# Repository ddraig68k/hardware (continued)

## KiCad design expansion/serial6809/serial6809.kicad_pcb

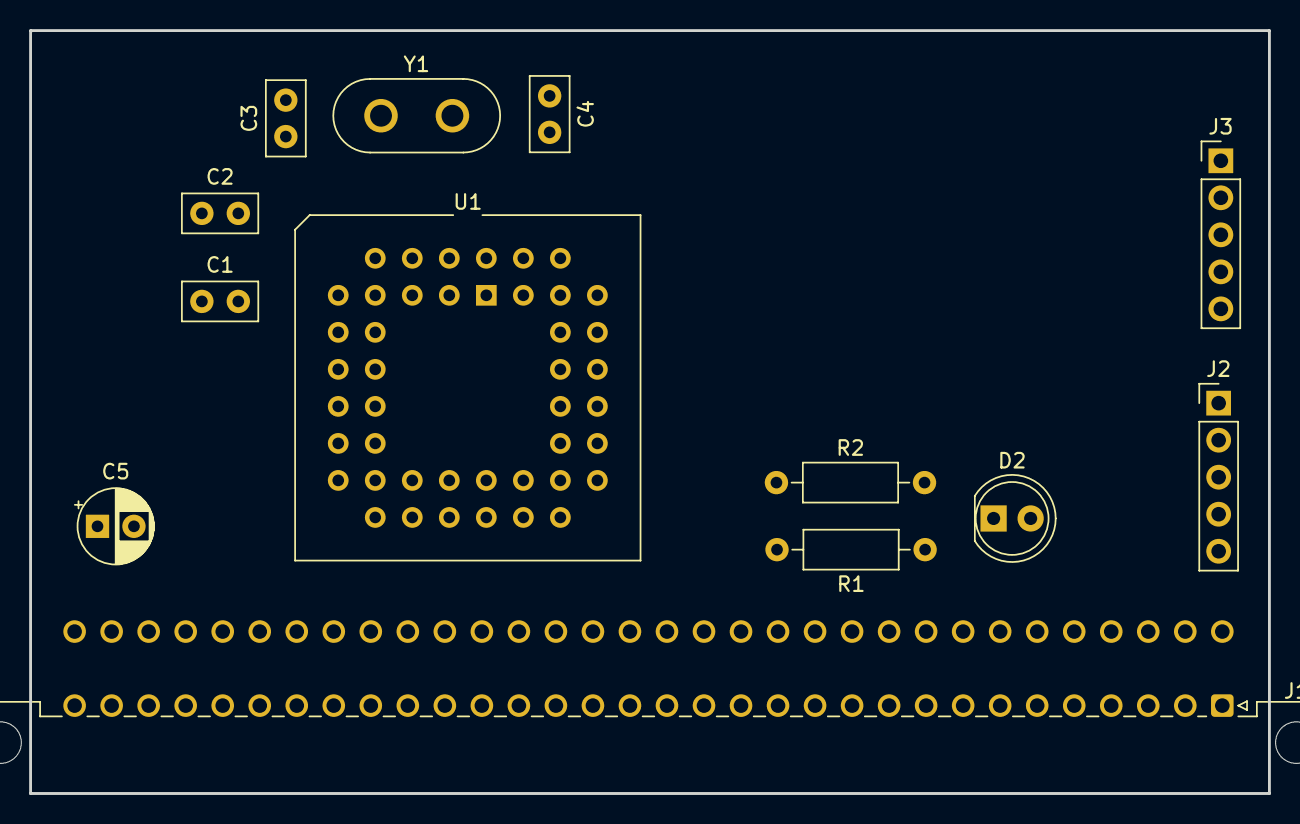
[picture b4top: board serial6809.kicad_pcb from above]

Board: 2 copper layers, 85.0 x 52.3 mm, 13 parts (0 on the bottom side), 30 nets, no tracks yet.

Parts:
C1, C2: 100nF; C_Disc_D5.0mm_W2.5mm_P2.50mm
C3, C4: 22pF; C_Disc_D5.0mm_W2.5mm_P2.50mm
C5: 47uF; CP_Radial_D5.0mm_P2.50mm
D2: GREEN; LED_D5.0mm
J1: Expansion; DIN41612_C_2x32_Male_Horizontal_THT
J2: Serial 2; PinHeader_1x05_P2.54mm_Vertical
J3: Serial 1; PinHeader_1x05_P2.54mm_Vertical
R1: 10K; R_Axial_DIN0207_L6.3mm_D2.5mm_P10.16mm_Horizontal
R2: 270R; R_Axial_DIN0207_L6.3mm_D2.5mm_P10.16mm_Horizontal
U1: SC26C92C1A; PLCC-44_THT-Socket
Y1: 3.6864Mhz; Crystal_HC50_Vertical

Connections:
+5V: C1.1, C2.1, C5.1, J1.A1, J1.C1, R1.1, U1.44 (VCC)
/A0: J1.C30, U1.2 (A0)
/A1: J1.C29, U1.4 (A1)
/A2: J1.C28, U1.6 (A2)
/A3: J1.C27, U1.7 (A3)
/CTSA: J3.4, U1.8 (IP0)
/CTSB: J2.4, U1.5 (IP1)
/D0: J1.A12, U1.28 (D0)
/D1: J1.A11, U1.18 (D1)
/D2: J1.A10, U1.27 (D2)
/D3: J1.A9, U1.19 (D3)
/D4: J1.A8, U1.26 (D4)
/D5: J1.A7, U1.20 (D5)
/D6: J1.A6, U1.25 (D6)
/D7: J1.A5, U1.21 (D7)
/RESET: J1.C6, U1.38 (RESET)
/RTSA: J3.3, U1.32 (OP0)
/RTSB: J2.3, U1.14 (OP1)
/RXDA: J3.1, U1.33 (TxDA)
/RXDB: J2.1, U1.13 (TxDB)
/TXDA: J3.2, U1.35 (RxDA)
/TXDB: J2.2, U1.11 (RxDB)
/~CS_EXP: D2.2 (A), J1.A15, U1.39 (~CE)
/~INT_EXP1: J1.A13, R1.2, U1.24 (~INTR)
/~RD: J1.A22, U1.10 (~RD)
/~WR: J1.A21, U1.9 (~WR)
GND: C1.2, C2.2, C3.2, C4.2, C5.2, J1.A31, J1.A32, J1.C31, J1.C32, J2.5, J3.5, R2.2, U1.22 (GND)
unnamed: D2.1 (K), R2.1
unnamed: C4.1, U1.36 (X1/CLK), Y1.2
unnamed: C3.1, U1.37 (X2), Y1.1

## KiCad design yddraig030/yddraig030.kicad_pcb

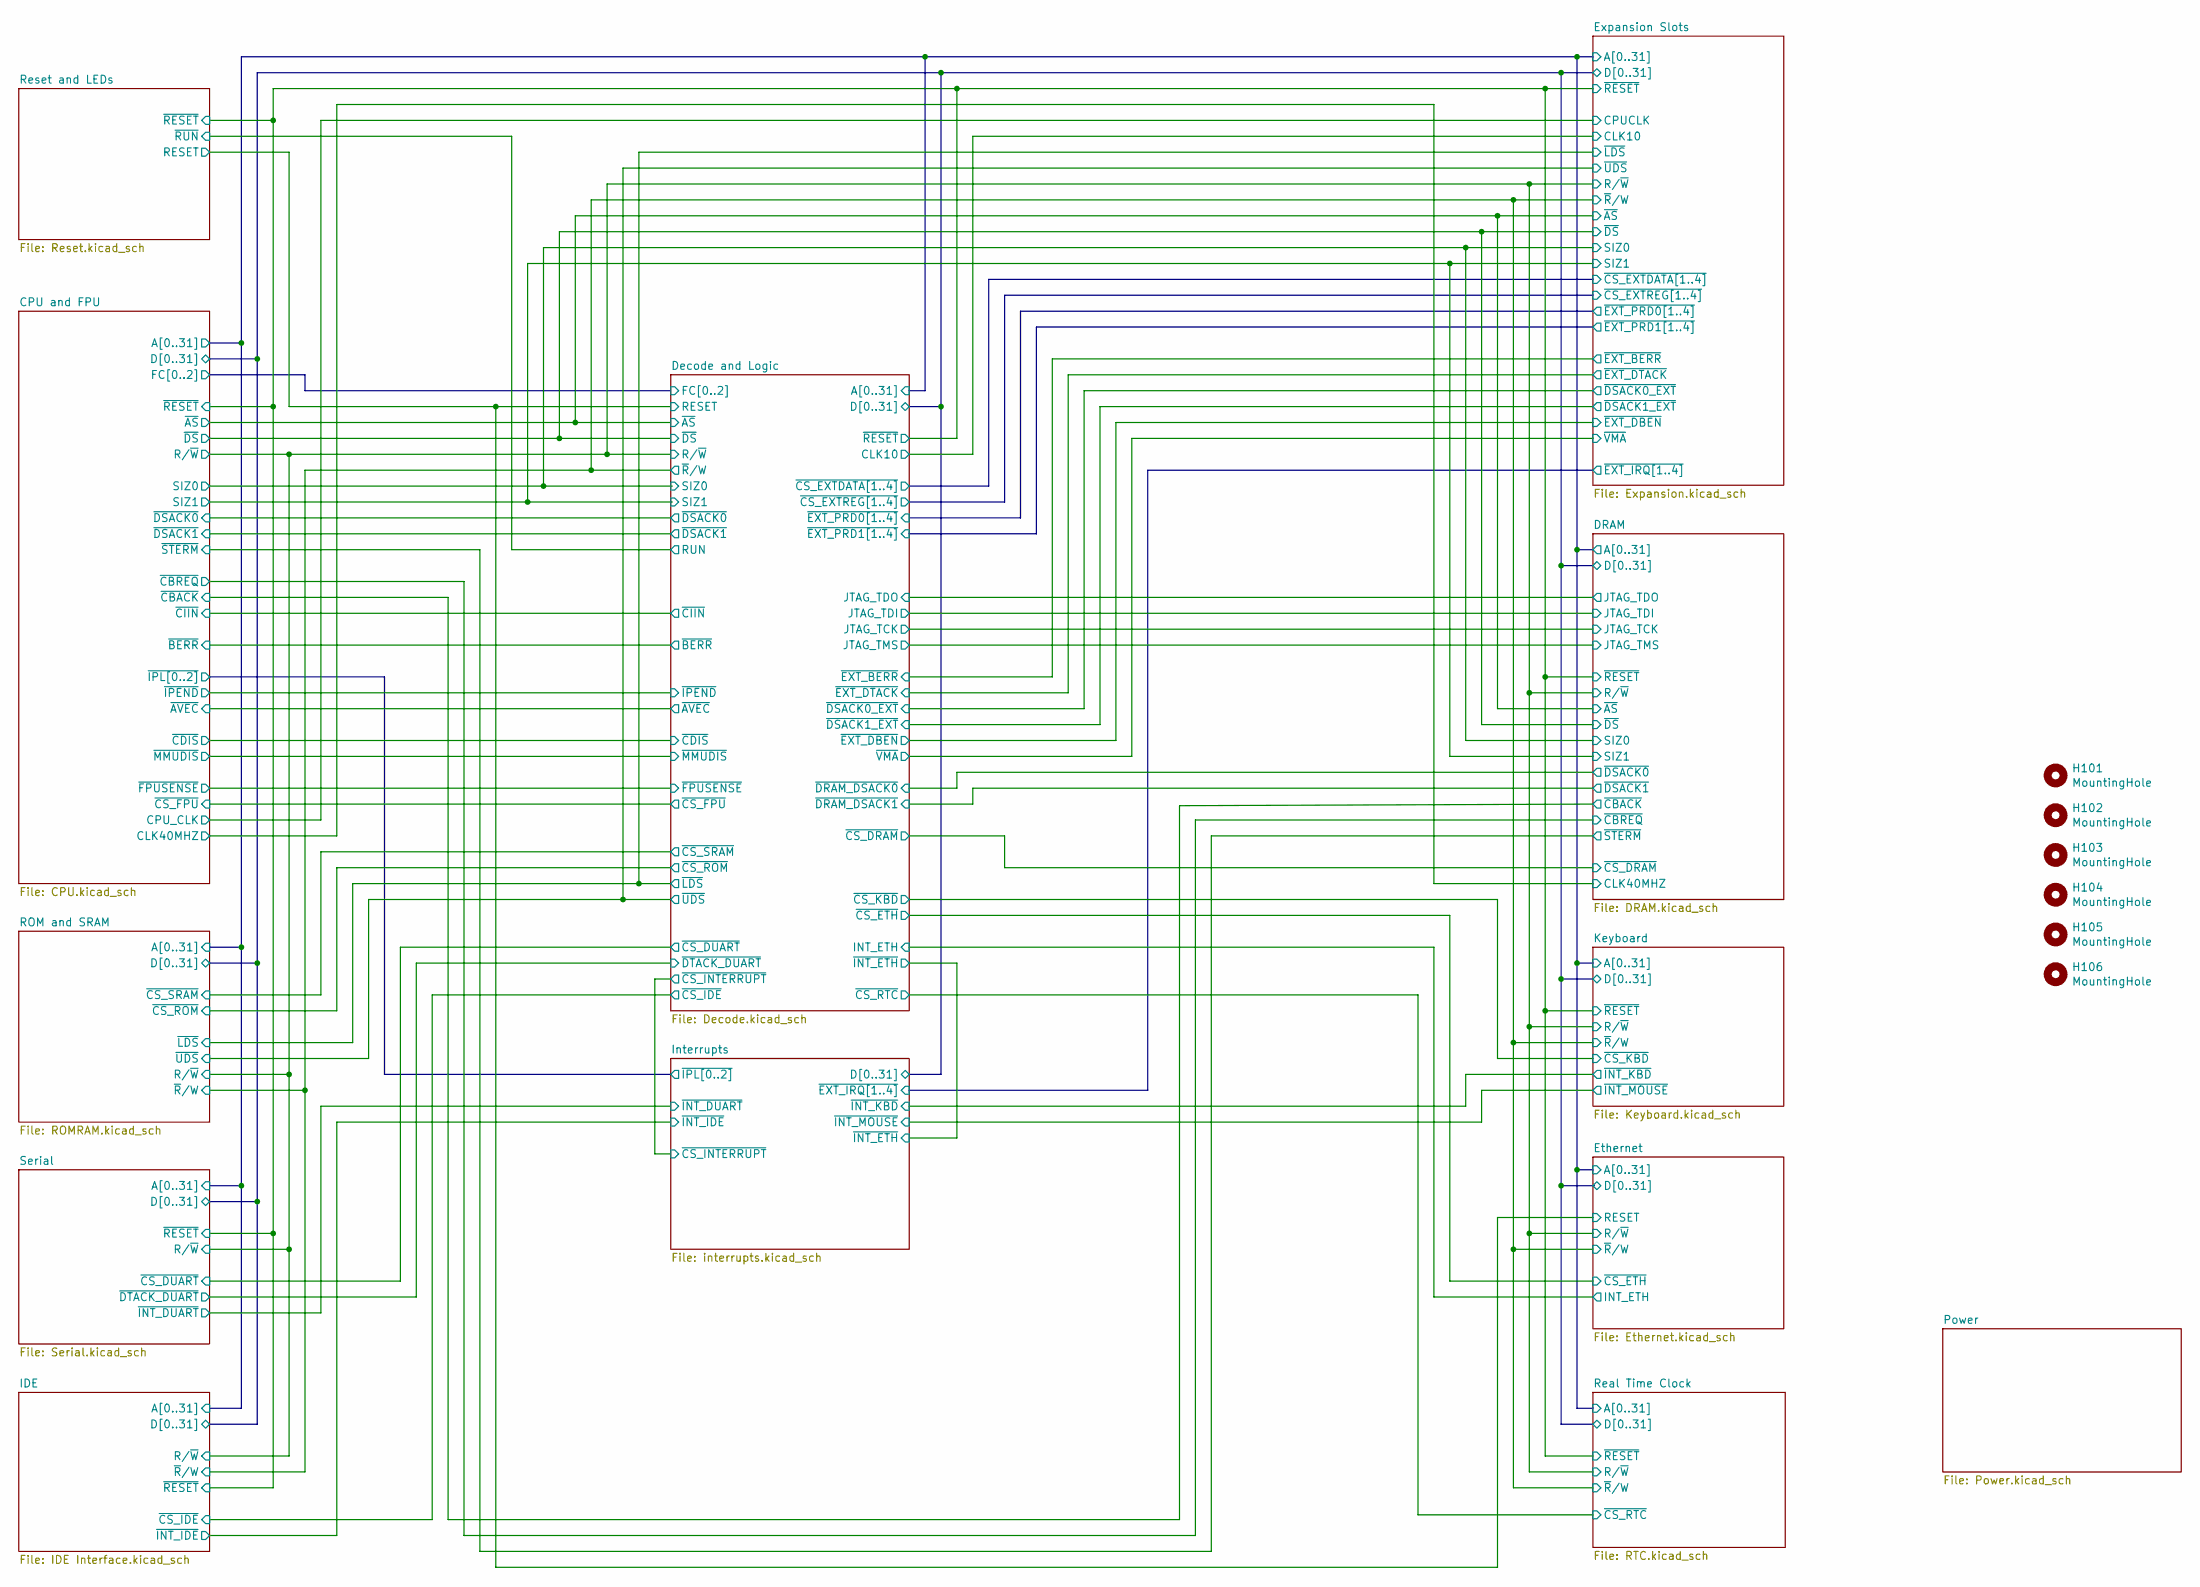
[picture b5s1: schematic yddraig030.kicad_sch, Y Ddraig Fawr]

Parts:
H101, H102, H103, H104, H105, H106: MountingHole; MountingHole_4.3mm_M4

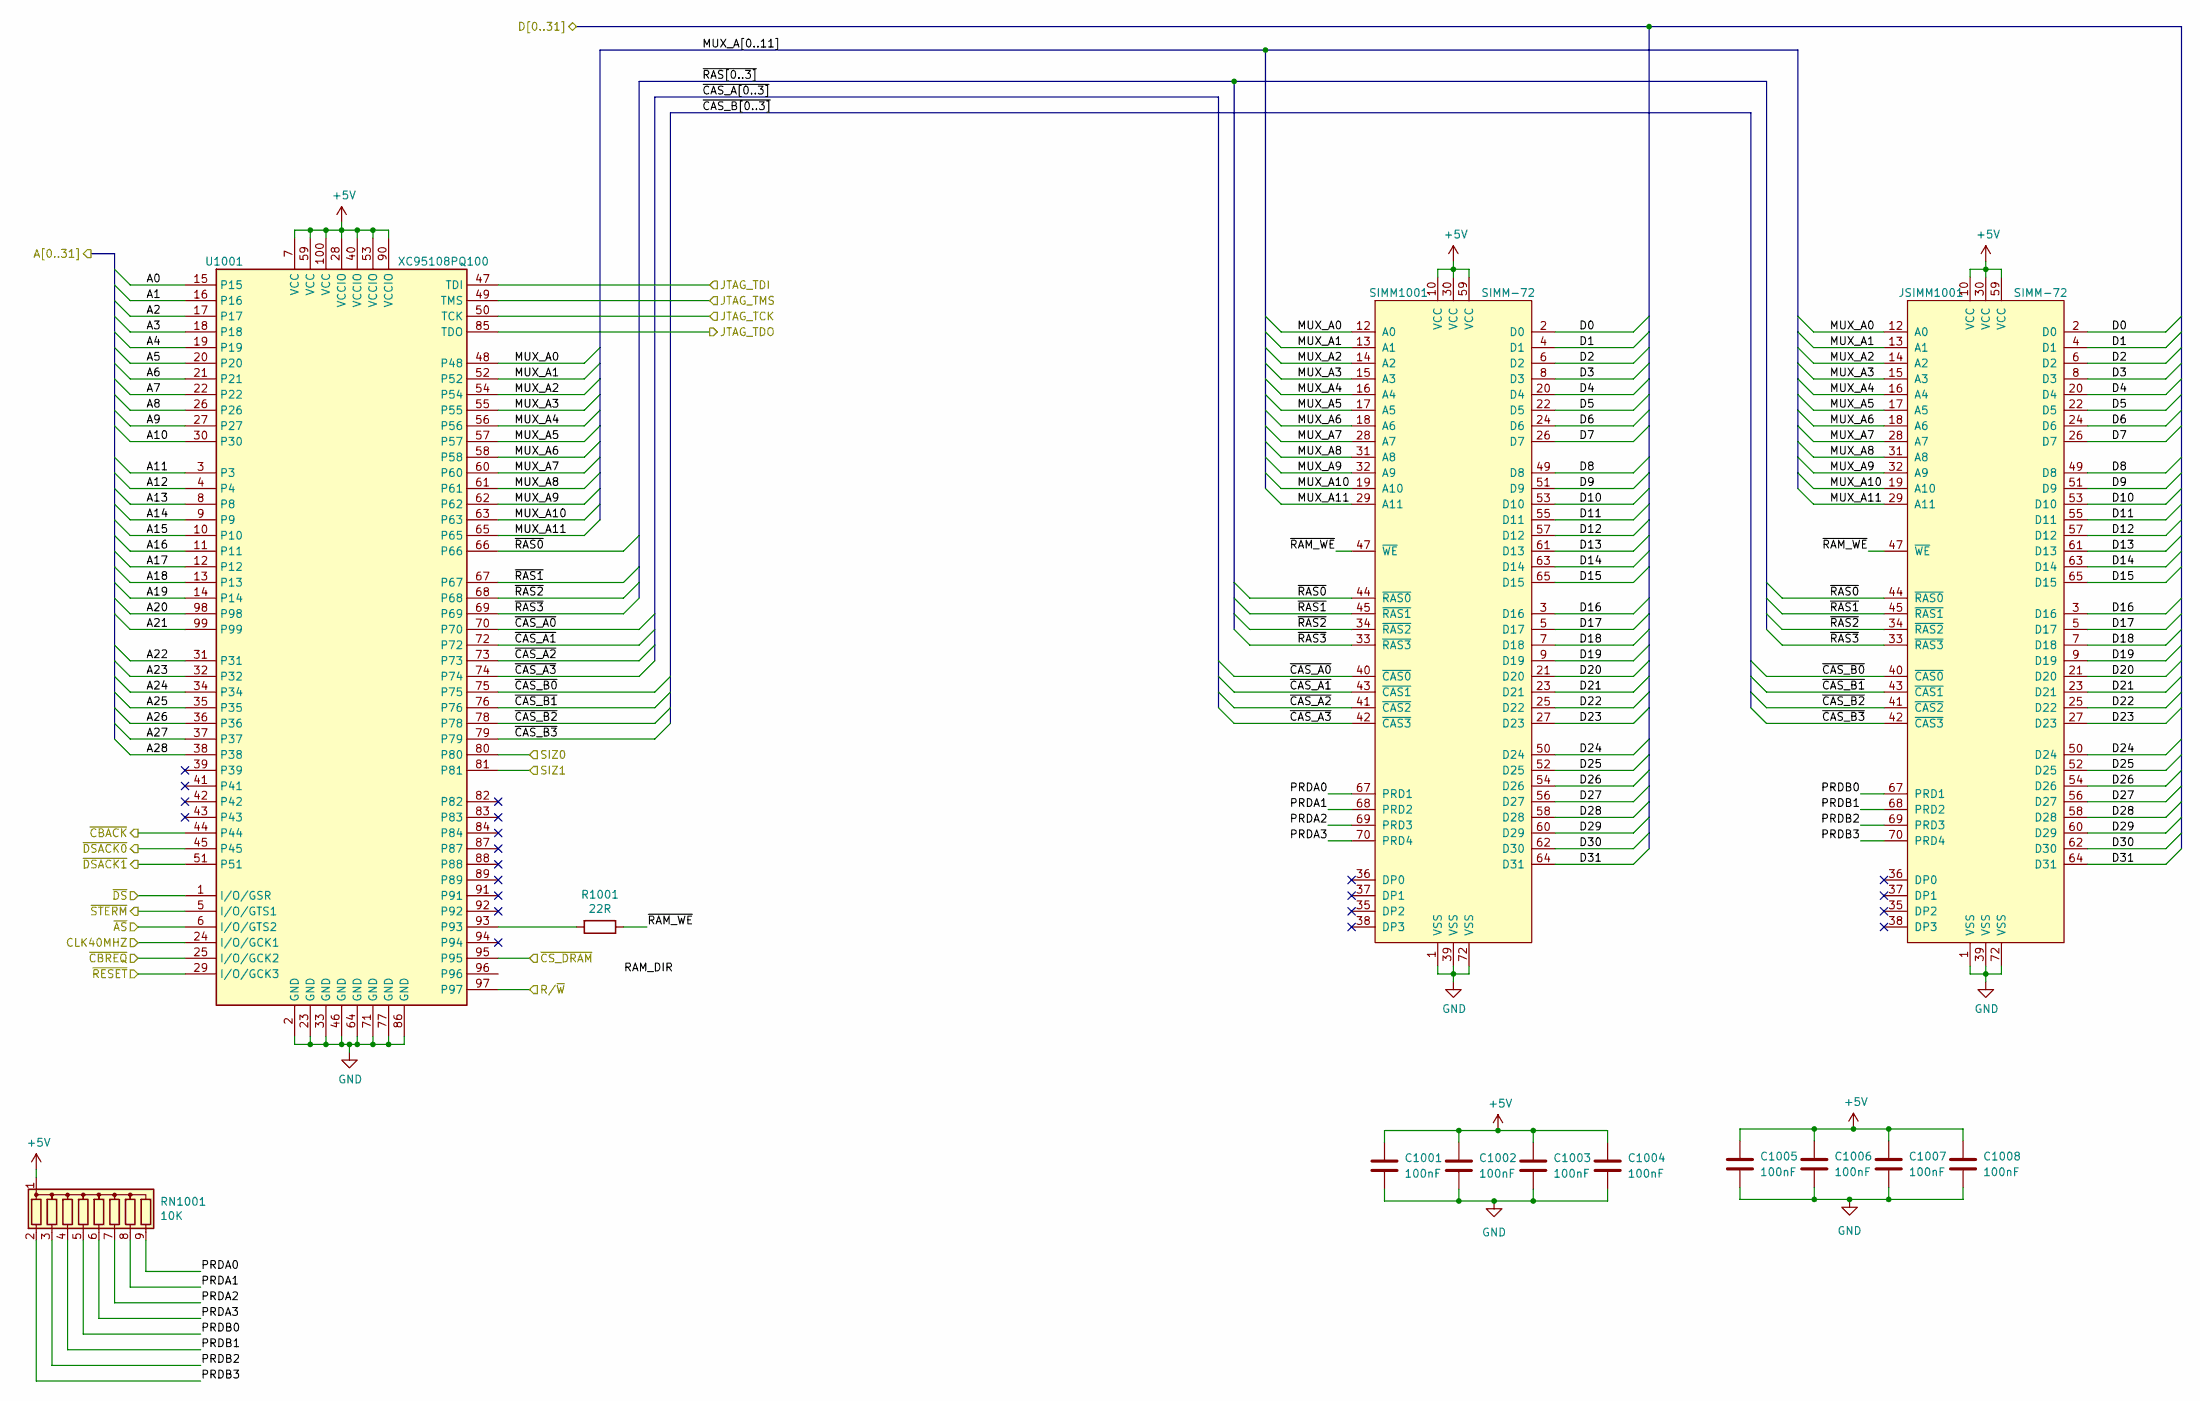
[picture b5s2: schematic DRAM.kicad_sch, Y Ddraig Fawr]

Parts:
C1001, C1002, C1003, C1004, C1005, C1006, C1007, C1008: 100nF; C_0805_2012Metric
JSIMM1001: SIMM-72; 58220214
R1001: 22R; R_0805_2012Metric
RN1001: 10K; R_Array_SIP9
SIMM1001: SIMM-72; 58220214
U1001: XC95108PQ100; RTL8019AS

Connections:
+5V: C1001.1, C1002.1, C1003.1, C1004.1, C1005.1, C1006.1, C1007.1, C1008.1, JSIMM1001.10 (VCC), JSIMM1001.30 (VCC), JSIMM1001.59 (VCC), RN1001.1 (common), SIMM1001.10 (VCC), SIMM1001.30 (VCC), SIMM1001.59 (VCC), U1001.7 (VCC), U1001.28 (VCCIO), U1001.40 (VCCIO), U1001.53 (VCCIO), U1001.59 (VCC), U1001.90 (VCCIO), U1001.100 (VCC); also elsewhere on the board
/CPU and FPU/CLK40MHZ: U1001.24 (I/O/GCK1); also elsewhere on the board
/CPU and FPU/R/~W: U1001.97; also elsewhere on the board
/CPU and FPU/SIZ0: U1001.80; also elsewhere on the board
/CPU and FPU/SIZ1: U1001.81; also elsewhere on the board
/CPU and FPU/~AS: U1001.6 (I/O/GTS2); also elsewhere on the board
/CPU and FPU/~CBACK: U1001.44; also elsewhere on the board
/CPU and FPU/~CBREQ: U1001.25 (I/O/GCK2); also elsewhere on the board
/CPU and FPU/~DS: U1001.1 (I/O/GSR); also elsewhere on the board
/CPU and FPU/~RESET: U1001.29 (I/O/GCK3); also elsewhere on the board
/CPU and FPU/~STERM: U1001.5 (I/O/GTS1); also elsewhere on the board
/DRAM/JTAG_TDI: U1001.47 (TDI); also elsewhere on the board
/DRAM/MUX_A0: JSIMM1001.12 (A0), SIMM1001.12 (A0), U1001.48
/DRAM/MUX_A1: JSIMM1001.13 (A1), SIMM1001.13 (A1), U1001.52
/DRAM/MUX_A2: JSIMM1001.14 (A2), SIMM1001.14 (A2), U1001.54
/DRAM/MUX_A3: JSIMM1001.15 (A3), SIMM1001.15 (A3), U1001.55
/DRAM/MUX_A4: JSIMM1001.16 (A4), SIMM1001.16 (A4), U1001.56
/DRAM/MUX_A5: JSIMM1001.17 (A5), SIMM1001.17 (A5), U1001.57
/DRAM/MUX_A6: JSIMM1001.18 (A6), SIMM1001.18 (A6), U1001.58
/DRAM/MUX_A7: JSIMM1001.28 (A7), SIMM1001.28 (A7), U1001.60
/DRAM/MUX_A8: JSIMM1001.31 (A8), SIMM1001.31 (A8), U1001.61
/DRAM/MUX_A9: JSIMM1001.32 (A9), SIMM1001.32 (A9), U1001.62
/DRAM/MUX_A10: JSIMM1001.19 (A10), SIMM1001.19 (A10), U1001.63
/DRAM/MUX_A11: JSIMM1001.29 (A11), SIMM1001.29 (A11), U1001.65
/DRAM/PRDA0: RN1001.9 (R8), SIMM1001.67 (PRD1)
/DRAM/PRDA1: RN1001.8 (R7), SIMM1001.68 (PRD2)
/DRAM/PRDA2: RN1001.7 (R6), SIMM1001.69 (PRD3)
/DRAM/PRDA3: RN1001.6 (R5), SIMM1001.70 (PRD4)
/DRAM/PRDB0: JSIMM1001.67 (PRD1), RN1001.5 (R4)
/DRAM/PRDB1: JSIMM1001.68 (PRD2), RN1001.4 (R3)
/DRAM/PRDB2: JSIMM1001.69 (PRD3), RN1001.3 (R2)
/DRAM/PRDB3: JSIMM1001.70 (PRD4), RN1001.2 (R1)
/DRAM/~CAS_A0: SIMM1001.40 (~CAS0), U1001.70
/DRAM/~CAS_A1: SIMM1001.43 (~CAS1), U1001.72
/DRAM/~CAS_A2: SIMM1001.41 (~CAS2), U1001.73
/DRAM/~CAS_A3: SIMM1001.42 (~CAS3), U1001.74
/DRAM/~CAS_B0: JSIMM1001.40 (~CAS0), U1001.75
/DRAM/~CAS_B1: JSIMM1001.43 (~CAS1), U1001.76
/DRAM/~CAS_B2: JSIMM1001.41 (~CAS2), U1001.78
/DRAM/~CAS_B3: JSIMM1001.42 (~CAS3), U1001.79
/DRAM/~CS_DRAM: U1001.95; also elsewhere on the board
/DRAM/~DSACK0: U1001.45; also elsewhere on the board
/DRAM/~DSACK1: U1001.51; also elsewhere on the board
/DRAM/~RAM_WE: JSIMM1001.47 (~WE), R1001.1, SIMM1001.47 (~WE)
/DRAM/~RAS0: JSIMM1001.44 (~RAS0), SIMM1001.44 (~RAS0), U1001.66
/DRAM/~RAS1: JSIMM1001.45 (~RAS1), SIMM1001.45 (~RAS1), U1001.67
/DRAM/~RAS2: JSIMM1001.34 (~RAS2), SIMM1001.34 (~RAS2), U1001.68
/DRAM/~RAS3: JSIMM1001.33 (~RAS3), SIMM1001.33 (~RAS3), U1001.69
/Decode and Logic/TCK: U1001.50 (TCK); also elsewhere on the board
/Decode and Logic/TDO: U1001.85 (TDO); also elsewhere on the board
/Decode and Logic/TMS: U1001.49 (TMS); also elsewhere on the board
/ROM and SRAM/A0: U1001.15; also elsewhere on the board
/ROM and SRAM/A1: U1001.16; also elsewhere on the board
/ROM and SRAM/A2: U1001.17; also elsewhere on the board
/ROM and SRAM/A3: U1001.18; also elsewhere on the board
/ROM and SRAM/A4: U1001.19; also elsewhere on the board
/ROM and SRAM/A5: U1001.20; also elsewhere on the board
/ROM and SRAM/A6: U1001.21; also elsewhere on the board
/ROM and SRAM/A7: U1001.22; also elsewhere on the board
/ROM and SRAM/A8: U1001.26; also elsewhere on the board
/ROM and SRAM/A9: U1001.27; also elsewhere on the board
/ROM and SRAM/A10: U1001.30; also elsewhere on the board
/ROM and SRAM/A11: U1001.3; also elsewhere on the board
/ROM and SRAM/A12: U1001.4; also elsewhere on the board
/ROM and SRAM/A13: U1001.8; also elsewhere on the board
/ROM and SRAM/A14: U1001.9; also elsewhere on the board
/ROM and SRAM/A15: U1001.10; also elsewhere on the board
/ROM and SRAM/A16: U1001.11; also elsewhere on the board
/ROM and SRAM/A17: U1001.12; also elsewhere on the board
/ROM and SRAM/A18: U1001.13; also elsewhere on the board
/ROM and SRAM/A19: U1001.14; also elsewhere on the board
/ROM and SRAM/A20: U1001.98; also elsewhere on the board
/ROM and SRAM/A21: U1001.99; also elsewhere on the board
/ROM and SRAM/A22: U1001.31; also elsewhere on the board
/ROM and SRAM/A23: U1001.32; also elsewhere on the board
/ROM and SRAM/A24: U1001.34; also elsewhere on the board
/ROM and SRAM/A25: U1001.35; also elsewhere on the board
/ROM and SRAM/A26: U1001.36; also elsewhere on the board
/ROM and SRAM/A27: U1001.37; also elsewhere on the board
/ROM and SRAM/A28: U1001.38; also elsewhere on the board
/ROM and SRAM/D0: JSIMM1001.2 (D0), SIMM1001.2 (D0); also elsewhere on the board
/ROM and SRAM/D1: JSIMM1001.4 (D1), SIMM1001.4 (D1); also elsewhere on the board
/ROM and SRAM/D2: JSIMM1001.6 (D2), SIMM1001.6 (D2); also elsewhere on the board
/ROM and SRAM/D3: JSIMM1001.8 (D3), SIMM1001.8 (D3); also elsewhere on the board
/ROM and SRAM/D4: JSIMM1001.20 (D4), SIMM1001.20 (D4); also elsewhere on the board
/ROM and SRAM/D5: JSIMM1001.22 (D5), SIMM1001.22 (D5); also elsewhere on the board
/ROM and SRAM/D6: JSIMM1001.24 (D6), SIMM1001.24 (D6); also elsewhere on the board
/ROM and SRAM/D7: JSIMM1001.26 (D7), SIMM1001.26 (D7); also elsewhere on the board
/ROM and SRAM/D8: JSIMM1001.49 (D8), SIMM1001.49 (D8); also elsewhere on the board
/ROM and SRAM/D9: JSIMM1001.51 (D9), SIMM1001.51 (D9); also elsewhere on the board
/ROM and SRAM/D10: JSIMM1001.53 (D10), SIMM1001.53 (D10); also elsewhere on the board
/ROM and SRAM/D11: JSIMM1001.55 (D11), SIMM1001.55 (D11); also elsewhere on the board
/ROM and SRAM/D12: JSIMM1001.57 (D12), SIMM1001.57 (D12); also elsewhere on the board
/ROM and SRAM/D13: JSIMM1001.61 (D13), SIMM1001.61 (D13); also elsewhere on the board
/ROM and SRAM/D14: JSIMM1001.63 (D14), SIMM1001.63 (D14); also elsewhere on the board
/ROM and SRAM/D15: JSIMM1001.65 (D15), SIMM1001.65 (D15); also elsewhere on the board
/ROM and SRAM/D16: JSIMM1001.3 (D16), SIMM1001.3 (D16); also elsewhere on the board
/ROM and SRAM/D17: JSIMM1001.5 (D17), SIMM1001.5 (D17); also elsewhere on the board
/ROM and SRAM/D18: JSIMM1001.7 (D18), SIMM1001.7 (D18); also elsewhere on the board
/ROM and SRAM/D19: JSIMM1001.9 (D19), SIMM1001.9 (D19); also elsewhere on the board
/ROM and SRAM/D20: JSIMM1001.21 (D20), SIMM1001.21 (D20); also elsewhere on the board
/ROM and SRAM/D21: JSIMM1001.23 (D21), SIMM1001.23 (D21); also elsewhere on the board
/ROM and SRAM/D22: JSIMM1001.25 (D22), SIMM1001.25 (D22); also elsewhere on the board
/ROM and SRAM/D23: JSIMM1001.27 (D23), SIMM1001.27 (D23); also elsewhere on the board
/ROM and SRAM/D24: JSIMM1001.50 (D24), SIMM1001.50 (D24); also elsewhere on the board
/ROM and SRAM/D25: JSIMM1001.52 (D25), SIMM1001.52 (D25); also elsewhere on the board
/ROM and SRAM/D26: JSIMM1001.54 (D26), SIMM1001.54 (D26); also elsewhere on the board
/ROM and SRAM/D27: JSIMM1001.56 (D27), SIMM1001.56 (D27); also elsewhere on the board
/ROM and SRAM/D28: JSIMM1001.58 (D28), SIMM1001.58 (D28); also elsewhere on the board
/ROM and SRAM/D29: JSIMM1001.60 (D29), SIMM1001.60 (D29); also elsewhere on the board
/ROM and SRAM/D30: JSIMM1001.62 (D30), SIMM1001.62 (D30); also elsewhere on the board
/ROM and SRAM/D31: JSIMM1001.64 (D31), SIMM1001.64 (D31); also elsewhere on the board
unnamed: R1001.2, U1001.93

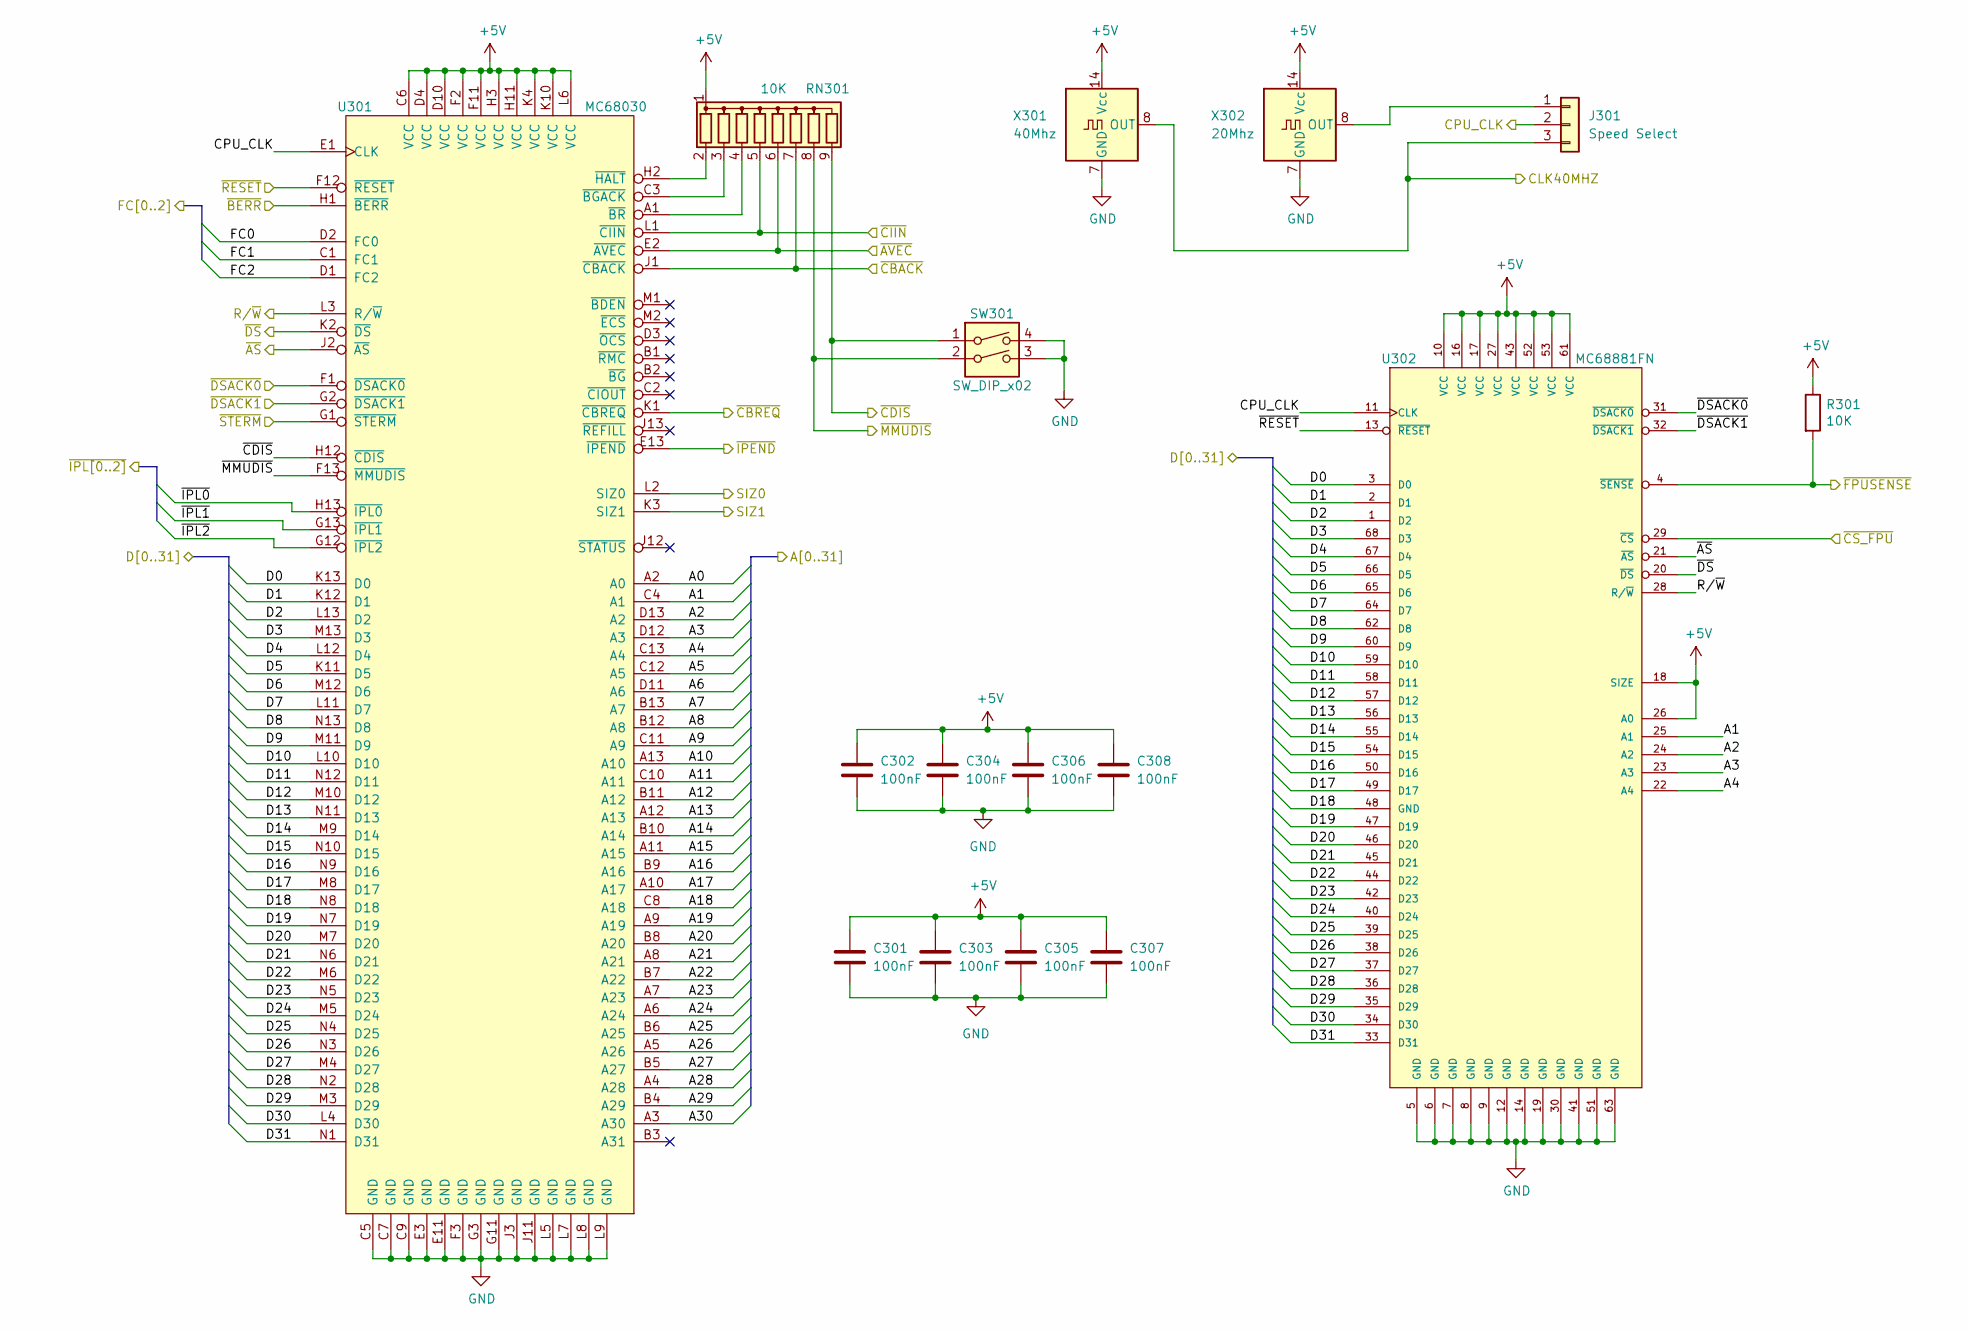
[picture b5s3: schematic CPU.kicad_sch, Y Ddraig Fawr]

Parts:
C301, C302, C303, C304, C305, C306, C307, C308: 100nF; C_0805_2012Metric
J301: Speed Select; PinHeader_1x03_P2.54mm_Vertical
R301: 10K; R_0805_2012Metric
RN301: 10K; R_Array_SIP9
SW301: SW_DIP_x02; DIP-4_W7.62mm
U301: MC68030; MC68030RC
U302: MC68881FN; PLCC-68_THT-Socket
X301: 40Mhz; Oscillator_DIP-14
X302: 20Mhz; Oscillator_DIP-14

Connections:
+5V: C301.1, C302.1, C303.1, C304.1, C305.1, C306.1, C307.1, C308.1, R301.1, RN301.1 (common), U301.C6 (VCC), U301.D4 (VCC), U301.D10 (VCC), U301.F2 (VCC), U301.F11 (VCC), U301.H3 (VCC), U301.H11 (VCC), U301.K4 (VCC), U301.K10 (VCC), U301.L6 (VCC), U302.10 (VCC), U302.16 (VCC), U302.17 (VCC), U302.18 (SIZE), U302.26 (A0), U302.27 (VCC), U302.43 (VCC), U302.52 (VCC), U302.53 (VCC), U302.61 (VCC), X301.14 (Vcc), X302.14 (Vcc); also elsewhere on the board
/CPU and FPU/CLK40MHZ: J301.3, X301.8 (OUT); also elsewhere on the board
/CPU and FPU/CPU_CLK: J301.2, U301.E1 (CLK), U302.11 (CLK); also elsewhere on the board
/CPU and FPU/FC0: U301.D2 (FC0); also elsewhere on the board
/CPU and FPU/FC1: U301.C1 (FC1); also elsewhere on the board
/CPU and FPU/FC2: U301.D1 (FC2); also elsewhere on the board
/CPU and FPU/R/~W: U301.L3 (R/~W), U302.28 (R/~W); also elsewhere on the board
/CPU and FPU/SIZ0: U301.L2 (SIZ0); also elsewhere on the board
/CPU and FPU/SIZ1: U301.K3 (SIZ1); also elsewhere on the board
/CPU and FPU/~AS: U301.J2 (~AS), U302.21 (~AS); also elsewhere on the board
/CPU and FPU/~AVEC: RN301.6 (R5), U301.E2 (~AVEC); also elsewhere on the board
/CPU and FPU/~BERR: U301.H1 (~BERR); also elsewhere on the board
/CPU and FPU/~CBACK: RN301.7 (R6), U301.J1 (~CBACK); also elsewhere on the board
/CPU and FPU/~CBREQ: U301.K1 (~CBREQ); also elsewhere on the board
/CPU and FPU/~CDIS: RN301.9 (R8), SW301.1, U301.H12 (~CDIS); also elsewhere on the board
/CPU and FPU/~CIIN: RN301.5 (R4), U301.L1 (~CIIN); also elsewhere on the board
/CPU and FPU/~CS_FPU: U302.29 (~CS); also elsewhere on the board
/CPU and FPU/~DSACK0: U301.F1 (~DSACK0), U302.31 (~DSACK0); also elsewhere on the board
/CPU and FPU/~DSACK1: U301.G2 (~DSACK1), U302.32 (~DSACK1); also elsewhere on the board
/CPU and FPU/~DS: U301.K2 (~DS), U302.20 (~DS); also elsewhere on the board
/CPU and FPU/~FPUSENSE: R301.2, U302.4 (~SENSE); also elsewhere on the board
/CPU and FPU/~IPEND: U301.E13 (~IPEND); also elsewhere on the board
/CPU and FPU/~IPL0: U301.H13 (~IPL0); also elsewhere on the board
/CPU and FPU/~IPL1: U301.G13 (~IPL1); also elsewhere on the board
/CPU and FPU/~IPL2: U301.G12 (~IPL2); also elsewhere on the board
/CPU and FPU/~MMUDIS: RN301.8 (R7), SW301.2, U301.F13 (~MMUDIS); also elsewhere on the board
/CPU and FPU/~RESET: U301.F12 (~RESET), U302.13 (~RESET); also elsewhere on the board
/CPU and FPU/~STERM: U301.G1 (~STERM); also elsewhere on the board
/ROM and SRAM/A0: U301.A2 (A0); also elsewhere on the board
/ROM and SRAM/A1: U301.C4 (A1), U302.25 (A1); also elsewhere on the board
/ROM and SRAM/A2: U301.D13 (A2), U302.24 (A2); also elsewhere on the board
/ROM and SRAM/A3: U301.D12 (A3), U302.23 (A3); also elsewhere on the board
/ROM and SRAM/A4: U301.C13 (A4), U302.22 (A4); also elsewhere on the board
/ROM and SRAM/A5: U301.C12 (A5); also elsewhere on the board
/ROM and SRAM/A6: U301.D11 (A6); also elsewhere on the board
/ROM and SRAM/A7: U301.B13 (A7); also elsewhere on the board
/ROM and SRAM/A8: U301.B12 (A8); also elsewhere on the board
/ROM and SRAM/A9: U301.C11 (A9); also elsewhere on the board
/ROM and SRAM/A10: U301.A13 (A10); also elsewhere on the board
/ROM and SRAM/A11: U301.C10 (A11); also elsewhere on the board
/ROM and SRAM/A12: U301.B11 (A12); also elsewhere on the board
/ROM and SRAM/A13: U301.A12 (A13); also elsewhere on the board
/ROM and SRAM/A14: U301.B10 (A14); also elsewhere on the board
/ROM and SRAM/A15: U301.A11 (A15); also elsewhere on the board
/ROM and SRAM/A16: U301.B9 (A16); also elsewhere on the board
/ROM and SRAM/A17: U301.A10 (A17); also elsewhere on the board
/ROM and SRAM/A18: U301.C8 (A18); also elsewhere on the board
/ROM and SRAM/A19: U301.A9 (A19); also elsewhere on the board
/ROM and SRAM/A20: U301.B8 (A20); also elsewhere on the board
/ROM and SRAM/A21: U301.A8 (A21); also elsewhere on the board
/ROM and SRAM/A22: U301.B7 (A22); also elsewhere on the board
/ROM and SRAM/A23: U301.A7 (A23); also elsewhere on the board
/ROM and SRAM/A24: U301.A6 (A24); also elsewhere on the board
/ROM and SRAM/A25: U301.B6 (A25); also elsewhere on the board
/ROM and SRAM/A26: U301.A5 (A26); also elsewhere on the board
/ROM and SRAM/A27: U301.B5 (A27); also elsewhere on the board
/ROM and SRAM/A28: U301.A4 (A28); also elsewhere on the board
/ROM and SRAM/A29: U301.B4 (A29); also elsewhere on the board
/ROM and SRAM/A30: U301.A3 (A30); also elsewhere on the board
/ROM and SRAM/D0: U301.K13 (D0), U302.3 (D0); also elsewhere on the board
/ROM and SRAM/D1: U301.K12 (D1), U302.2 (D1); also elsewhere on the board
/ROM and SRAM/D2: U301.L13 (D2), U302.1 (D2); also elsewhere on the board
/ROM and SRAM/D3: U301.M13 (D3), U302.68 (D3); also elsewhere on the board
/ROM and SRAM/D4: U301.L12 (D4), U302.67 (D4); also elsewhere on the board
/ROM and SRAM/D5: U301.K11 (D5), U302.66 (D5); also elsewhere on the board
/ROM and SRAM/D6: U301.M12 (D6), U302.65 (D6); also elsewhere on the board
/ROM and SRAM/D7: U301.L11 (D7), U302.64 (D7); also elsewhere on the board
/ROM and SRAM/D8: U301.N13 (D8), U302.62 (D8); also elsewhere on the board
/ROM and SRAM/D9: U301.M11 (D9), U302.60 (D9); also elsewhere on the board
/ROM and SRAM/D10: U301.L10 (D10), U302.59 (D10); also elsewhere on the board
/ROM and SRAM/D11: U301.N12 (D11), U302.58 (D11); also elsewhere on the board
/ROM and SRAM/D12: U301.M10 (D12), U302.57 (D12); also elsewhere on the board
/ROM and SRAM/D13: U301.N11 (D13), U302.56 (D13); also elsewhere on the board
/ROM and SRAM/D14: U301.M9 (D14), U302.55 (D14); also elsewhere on the board
/ROM and SRAM/D15: U301.N10 (D15), U302.54 (D15); also elsewhere on the board
/ROM and SRAM/D16: U301.N9 (D16), U302.50 (D16); also elsewhere on the board
/ROM and SRAM/D17: U301.M8 (D17), U302.49 (D17); also elsewhere on the board
/ROM and SRAM/D18: U301.N8 (D18), U302.48 (GND); also elsewhere on the board
/ROM and SRAM/D19: U301.N7 (D19), U302.47 (D19); also elsewhere on the board
/ROM and SRAM/D20: U301.M7 (D20), U302.46 (D20); also elsewhere on the board
/ROM and SRAM/D21: U301.N6 (D21), U302.45 (D21); also elsewhere on the board
/ROM and SRAM/D22: U301.M6 (D22), U302.44 (D22); also elsewhere on the board
/ROM and SRAM/D23: U301.N5 (D23), U302.42 (D23); also elsewhere on the board
/ROM and SRAM/D24: U301.M5 (D24), U302.40 (D24); also elsewhere on the board
/ROM and SRAM/D25: U301.N4 (D25), U302.39 (D25); also elsewhere on the board
/ROM and SRAM/D26: U301.N3 (D26), U302.38 (D26); also elsewhere on the board
/ROM and SRAM/D27: U301.M4 (D27), U302.37 (D27); also elsewhere on the board
/ROM and SRAM/D28: U301.N2 (D28), U302.36 (D28); also elsewhere on the board
/ROM and SRAM/D29: U301.M3 (D29), U302.35 (D29); also elsewhere on the board
/ROM and SRAM/D30: U301.L4 (D30), U302.34 (D30); also elsewhere on the board
/ROM and SRAM/D31: U301.N1 (D31), U302.33 (D31); also elsewhere on the board
unnamed: J301.1, X302.8 (OUT)
unnamed: RN301.2 (R1), U301.H2 (~HALT)
unnamed: RN301.3 (R2), U301.C3 (~BGACK)
unnamed: RN301.4 (R3), U301.A1 (~BR)
